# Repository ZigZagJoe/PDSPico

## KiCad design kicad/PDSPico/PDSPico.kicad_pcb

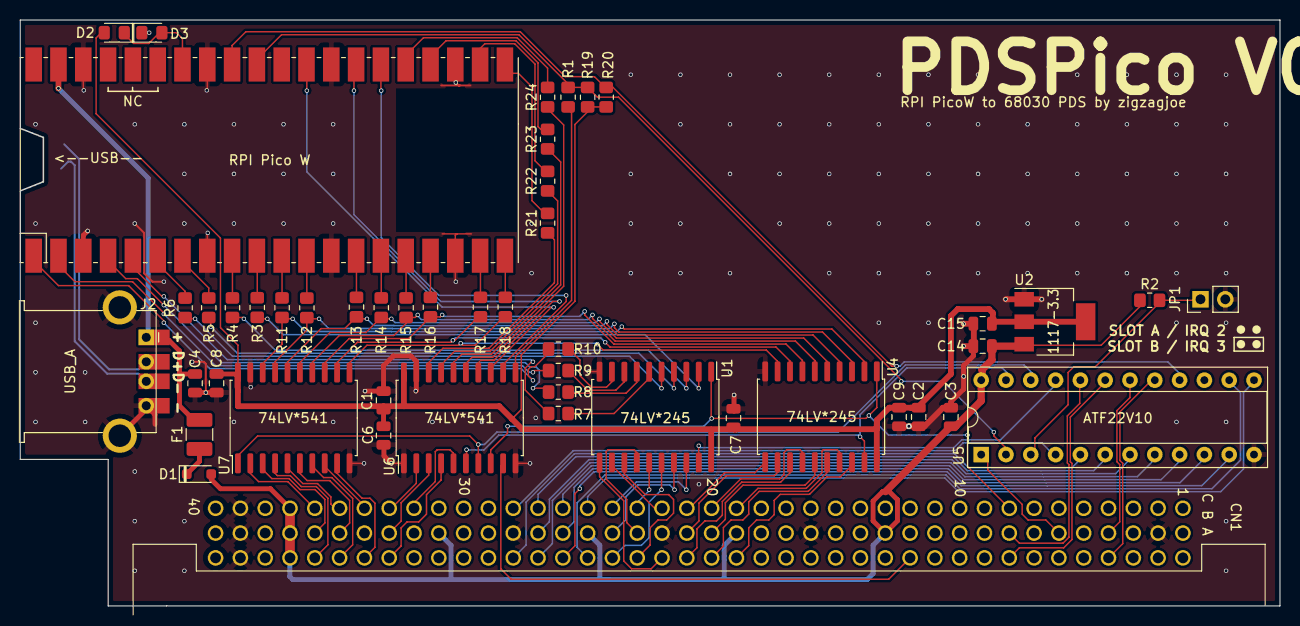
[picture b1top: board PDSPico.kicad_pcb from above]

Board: 2 copper layers, 129.0 x 59.9 mm, 49 parts (1 on the bottom side), 103 nets.

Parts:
C1, C2: 22uF; C_0805_2012Metric
C3, C6, C7, C8, C9: 220nf; C_0805_2012Metric
C4, C14, C15: 22uf; C_0805_2012Metric
CN1: PDS_LB_MALE; 650949-5 RA MALE
D1: D_Schottky; D_SOD-323_HandSoldering
D2: RED; LED_0805_2012Metric_Pad1.15x1.40mm_HandSolder
D3: GRN; LED_0805_2012Metric_Pad1.15x1.40mm_HandSolder
F1: 1.1A 6V; Fuse_1210_3225Metric_Pad1.42x2.65mm_HandSolder
J2: USB_A; USB_A_Horizontal_Generic
JP1: SLOT; PinHeader_1x02_P2.54mm_Vertical
R1: 1K; R_0805_2012Metric_Pad1.20x1.40mm_HandSolder
R2, R19, R20: 4.7K; R_0805_2012Metric_Pad1.20x1.40mm_HandSolder
R3, R4, R5, R6, R7, R8, R9, R10, R11, R12, R13, R14, R15, R16, R17, R18, R21, R22, R23, R24: 200; R_0805_2012Metric_Pad1.20x1.40mm_HandSolder
TP1: USB_DATA; TestPoint-2 RRect 1.5mmX2mm
U1, U4: 74LV*245; SOIC-20W_7.5x12.8mm_P1.27mm
U2: 1117-3.3; SOT-223-3_TabPin2
U3: RPI Pico W; RPi_Pico_SMD
U5: ATF22V10; DIP-24_W7.62mm_Socket
U6, U7: 74LV*541; SOIC-20W_7.5x12.8mm_P1.27mm

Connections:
+3V3: C1.1, C2.1, C6.1, C7.1, C8.1, C9.1, C15.1, D2.2 (A), R19.2, R20.1, U1.20 (VCC), U2.2 (VO), U4.20 (VCC), U6.20 (VCC), U7.20 (VCC)
+5V: C3.1, C14.1, CN1.A37 (+5V), CN1.B13 (+5V), CN1.B19 (+5V), CN1.B25 (+5V), CN1.B31 (+5V), CN1.B37 (+5V), CN1.C37 (+5V), D1.2 (A), R2.1, U2.3 (VI), U5.24 (VCC)
/A0: CN1.C36 (A0), U7.2 (A0)
/A1: CN1.B36 (A1), U7.3 (A1)
/A2: CN1.A36 (A2), U7.4 (A2)
/A3: CN1.C35 (A3), U7.5 (A3)
/A4: CN1.B35 (A4), U7.6 (A4)
/A5: CN1.A35 (A5), U7.7 (A5)
/A6: CN1.C34 (A6), U7.8 (A6)
/A7: CN1.A34 (A7), U7.9 (A7)
/A8: CN1.C33 (A8), U6.2 (A0)
/A9: CN1.B33 (A9), U6.3 (A1)
/A10: CN1.A33 (A10), U6.4 (A2)
/A11: CN1.C32 (A11), U6.5 (A3)
/A22: CN1.C28 (A22), U5.4 (I3/PD)
/A23: CN1.A28 (A23), U5.5 (I4)
/A24: CN1.C27 (A24), U5.6 (I5)
/A25: CN1.B27 (A25), U5.7 (I6)
/A26: CN1.A27 (A26), U5.8 (I7)
/A27: CN1.C26 (A27), U5.9 (I8)
/A28: CN1.B26 (A28), U5.10 (I9)
/A29: CN1.A26 (A29), U5.11 (I10)
/A30: CN1.C25 (A30), U5.13 (I11/~OE)
/A31: CN1.A25 (A31), U5.14 (IO10)
/BA8: R21.1, U6.18 (Y0)
/BA9: R22.1, U6.17 (Y1)
/BA10: R23.1, U6.16 (Y2)
/BA11: R24.1, U6.15 (Y3)
/BD0: R10.1, U3.1 (GPIO0)
/BD1: R9.1, U3.2 (GPIO1)
/BD2: R8.1, U3.4 (GPIO2)
/BD3: R7.1, U3.5 (GPIO3)
/BD4: R6.1, U3.6 (GPIO4)
/BD5: R5.1, U3.7 (GPIO5)
/BD6: R4.1, U3.9 (GPIO6)
/BD7: R3.1, U3.10 (GPIO7)
/BD8: R11.1, U3.11 (GPIO8)
/BD9: R12.1, U3.12 (GPIO9)
/BD10: R13.1, U3.14 (GPIO10)
/BD11: R14.1, U3.15 (GPIO11)
/BD12: R15.1, U3.16 (GPIO12)
/BD13: R16.1, U3.17 (GPIO13)
/BD14: R17.1, U3.19 (GPIO14)
/BD15: R18.1, U3.20 (GPIO15)
/B_RESET: R1.2, U6.11 (Y7)
/B_R/W: U3.26 (GPIO20), U6.12 (Y6)
/B_SEL.PICO: U3.27 (GPIO21), U6.14 (Y4)
/B_SEL.ROM: U3.29 (GPIO22), U6.13 (Y5)
/D16: CN1.A19 (D16), U4.18 (B0)
/D17: CN1.C19 (D17), U4.17 (B1)
/D18: CN1.A20 (D18), U4.16 (B2)
/D19: CN1.B20 (D19), U4.15 (B3)
/D20: CN1.C20 (D20), U4.14 (B4)
/D21: CN1.A21 (D21), U4.13 (B5)
/D22: CN1.B21 (D22), U4.12 (B6)
/D23: CN1.C21 (D23), U4.11 (B7)
/D24: CN1.A22 (D24), U1.11 (B7)
/D25: CN1.C22 (D25), U1.12 (B6)
/D26: CN1.A23 (D26), U1.13 (B5)
/D27: CN1.B23 (D27), U1.14 (B4)
/D28: CN1.C23 (D28), U1.15 (B3)
/D29: CN1.A24 (D29), U1.16 (B2)
/D30: CN1.B24 (D30), U1.17 (B1)
/D31: CN1.C24 (D31), U1.18 (B0)
/D+: J2.3 (D+), TP1.1
/D-: J2.2 (D-), TP1.2
/DS: CN1.B6 (~DS), U5.1 (I/CLK)
/DSACK0: CN1.B8 (~DSACK0), U5.20 (IO4)
/DSACK1: CN1.A8 (~DSACK1), U5.19 (IO5)
/DSACK.PICO: R1.1, R19.1, U3.31 (GPIO26_ADC0), U5.2 (I1)
/IRQ2: CN1.B4 (~IRQ2), U5.18 (IO6)
/IRQ3: CN1.A4 (~IRQ3), U5.17 (IO7)
/IRQ.PICO: R20.2, U3.32 (GPIO27_ADC1), U5.16 (IO8)
/LED_OUT: D2.1 (K), D3.2 (A), U3.34 (GPIO28_ADC2)
/PICO_VSYS: C4.1, F1.2, J2.1 (VBUS), U3.39 (VSYS)
/RESET: CN1.A12 (~RESET), U6.9 (A7)
/R/W: CN1.C8 (R/~W), U1.1 (A->B), U4.1 (A->B), U6.8 (A6)
/SEL.PICO: U4.19 (CE), U5.23 (IO1), U6.6 (A4)
/SEL.ROM: U5.22 (IO2), U6.7 (A5), U7.1 (G1)
/SEL.SLOT: U1.19 (CE), U5.21 (I03)
/SLOT_ID: JP1.1 (A), R2.2, U5.3 (I2)
GND: C1.2, C2.2, C3.2, C4.2, C6.2, C7.2, C8.2, C9.2, C14.2, C15.2, CN1.A39 (GND), CN1.B2 (GND), CN1.B16 (GND), CN1.B22 (GND), CN1.B28 (GND), CN1.B34 (GND), CN1.B39 (GND), CN1.C39 (GND), D3.1 (K), J2.4 (GND), J2.5 (Shield), JP1.2 (B), U1.10 (GND), U2.1 (GND), U3.3 (GND), U3.8 (GND), U3.13 (GND), U3.18 (GND), U3.23 (GND), U3.28 (GND), U3.33 (AGND), U3.38 (GND), U4.10 (GND), U5.12 (GND), U6.1 (G1), U6.10 (GND), U6.19 (G2), U7.10 (GND), U7.19 (G2)
unnamed: D1.1 (K), F1.1
unnamed: R3.2, U1.2 (A0)
unnamed: R4.2, U1.3 (A1)
unnamed: R5.2, U1.4 (A2)
unnamed: R6.2, U1.5 (A3)
unnamed: R7.2, U1.6 (A4)
unnamed: R8.2, U1.7 (A5)
unnamed: R9.2, U1.8 (A6)
unnamed: R10.2, U1.9 (A7)
unnamed: R21.2, U3.21 (GPIO16)
unnamed: R22.2, U3.22 (GPIO17)
unnamed: R23.2, U3.24 (GPIO18)
unnamed: R24.2, U3.25 (GPIO19)
unnamed: R11.2, U4.2 (A0), U7.18 (Y0)
unnamed: R12.2, U4.3 (A1), U7.17 (Y1)
unnamed: R13.2, U4.4 (A2), U7.16 (Y2)
unnamed: R14.2, U4.5 (A3), U7.15 (Y3)
unnamed: R15.2, U4.6 (A4), U7.14 (Y4)
unnamed: R16.2, U4.7 (A5), U7.13 (Y5)
unnamed: R17.2, U4.8 (A6), U7.12 (Y6)
unnamed: R18.2, U4.9 (A7), U7.11 (Y7)

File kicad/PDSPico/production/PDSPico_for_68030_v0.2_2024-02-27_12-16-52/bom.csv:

Designator,Footprint,Quantity,Value,LCSC Part #
"C1, C14, C15, C2, C4",0805,5,22uF,C45783
"C3, C6, C7, C8, C9",0805,5,220nf,C5378
CN1,650949-5 RA MALE,1,PDS_LB_MALE,C3652939
D1,D_SOD-323_HandSoldering,1,D_Schottky,C191023
D2,0805,1,RED,C84256
D3,0805,1,GRN,C2297
F1,1210,1,1.1A 6V,C2649912
J2,USB_A_Horizontal_Generic,1,USB_A,C720525
JP1,PinHeader_1x02_P2.54mm_Vertical,1,SLOT,N/A
R1,0805,1,1K,C17513
"R10, R11, R12, R13, R14, R15, R16, R17, R18, R21, R22, R23, R24, R3, R4, R5, R6, R7, R8, R9",0805,20,200,C17540
"R19, R2, R20",0805,3,4.7K,C17673
TP1,TestPoint-2 RRect 1.5mmX2mm,1,USB_DATA,N/A
"U1, U4",SOIC-20W_7.5x12.8mm_P1.27mm,2,74LV*245,C571201
U2,SOT-223-3_TabPin2,1,1117-3.3,C6186
U3,RPi_Pico_SMD,1,RPI Pico W,N/A
U5,DIP-24_W7.62mm_Socket,1,ATF22V10,C146581
"U6, U7",SOIC-20W_7.5x12.8mm_P1.27mm,2,74LV*541,C2652110

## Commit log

2024-02-27 remove files
2024-02-27 add schematic
2024-02-27 finish lame testbed code for hardware validation
